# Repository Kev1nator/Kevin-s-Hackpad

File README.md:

# Kevin's-Hackpad

My hackpad includes 12 Keys, 1 Knob, a screen and a few LED's!

#3D Model

#PCB
Schematic:

PCB:

#Firmware
This hackpad uses [QMK](https://qmk.fm/) firmware for everything. 
-The rotary encoder cahnges volume. 
-The keys act as shortcuts for opening apps, exectuing commands, ...
-The OLED shows the time.

#BOM:
Here you can find all the parts you need for this hackpad

- 4x Cherry MX Switches
- 4x DSA Keycaps
- 8x WS2812B LEDs
- 1x 0.91" 128x32 OLED Display
- 1x EC11 Rotary Encoder
- 1x XIAO RP2040
- 1x Case (3 printed parts)

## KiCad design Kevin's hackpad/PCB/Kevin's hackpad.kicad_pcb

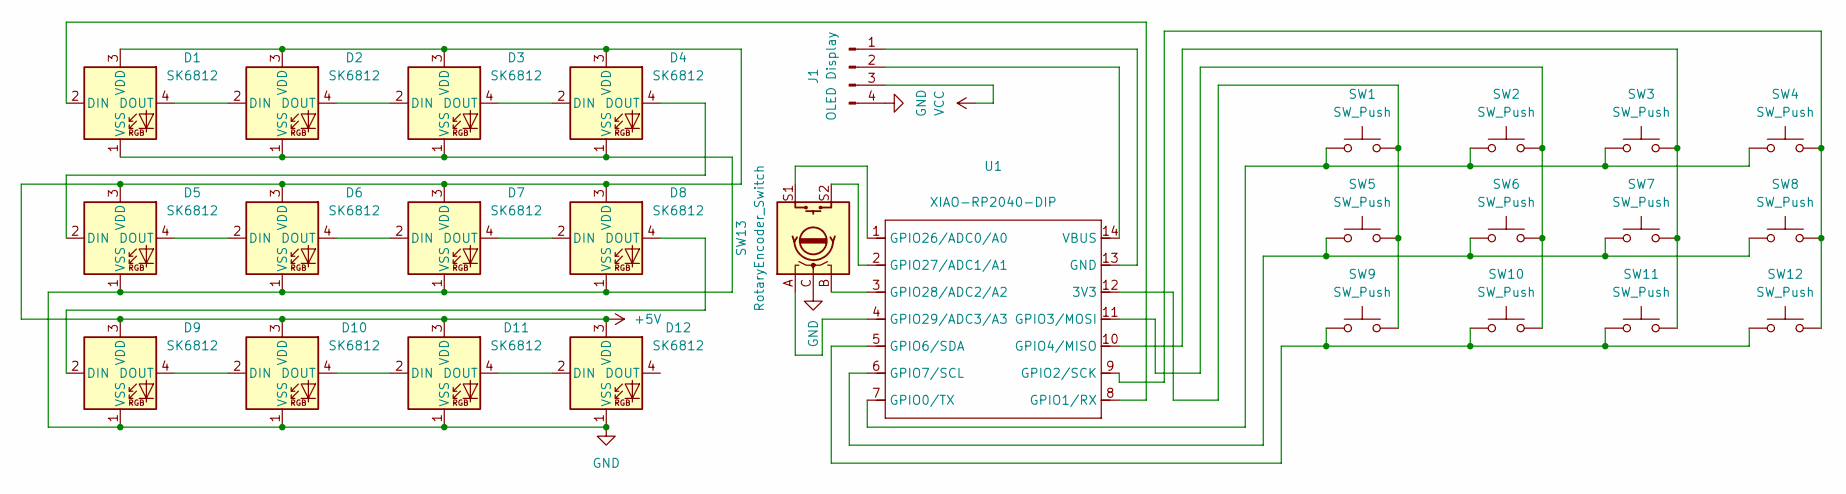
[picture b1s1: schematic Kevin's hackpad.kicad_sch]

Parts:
D1, D2, D3, D4, D5, D6, D7, D8, D9, D10, D11, D12: SK6812; LED_SK6812MINI_PLCC4_3.5x3.5mm_P1.75mm
J1: OLED Display; SSD1306-0.91-OLED-4pin-128x32
SW1, SW2, SW3, SW4, SW5, SW6, SW7, SW8, SW9, SW10, SW11, SW12: SW_Push; SW_Cherry_MX_1.00u_PCB
SW13: RotaryEncoder_Switch; RotaryEncoder_Alps_EC11E-Switch_Vertical_H20mm
U1: XIAO-RP2040-DIP

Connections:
+5V: D1.3 (VDD), D2.3 (VDD), D3.3 (VDD), D4.3 (VDD), D5.3 (VDD), D6.3 (VDD), D7.3 (VDD), D8.3 (VDD), D9.3 (VDD), D10.3 (VDD), D11.3 (VDD), D12.3 (VDD)
GND: D1.1 (VSS), D2.1 (VSS), D3.1 (VSS), D4.1 (VSS), D5.1 (VSS), D6.1 (VSS), D7.1 (VSS), D8.1 (VSS), D9.1 (VSS), D10.1 (VSS), D11.1 (VSS), D12.1 (VSS), J1.4, SW13.C
unnamed: D1.2 (DIN), U1.8 (GPIO1/RX)
unnamed: D1.4 (DOUT), D2.2 (DIN)
unnamed: D2.4 (DOUT), D3.2 (DIN)
unnamed: D3.4 (DOUT), D4.2 (DIN)
unnamed: D4.4 (DOUT), D5.2 (DIN)
unnamed: D5.4 (DOUT), D6.2 (DIN)
unnamed: D6.4 (DOUT), D7.2 (DIN)
unnamed: D7.4 (DOUT), D8.2 (DIN)
unnamed: D8.4 (DOUT), D9.2 (DIN)
unnamed: D9.4 (DOUT), D10.2 (DIN)
unnamed: D10.4 (DOUT), D11.2 (DIN)
unnamed: D11.4 (DOUT), D12.2 (DIN)
unnamed: J1.1, U1.13 (GND)
unnamed: J1.2, U1.14 (VBUS)
unnamed: SW1.2, SW5.2, SW9.2, U1.12 (3V3)
unnamed: SW1.1, SW2.1, SW3.1, SW4.1, U1.7 (GPIO0/TX)
unnamed: SW4.2, SW8.2, SW12.2, U1.9 (GPIO2/SCK)
unnamed: SW2.2, SW6.2, SW10.2, U1.11 (GPIO3/MOSI)
unnamed: SW3.2, SW7.2, SW11.2, U1.10 (GPIO4/MISO)
unnamed: SW9.1, SW10.1, SW11.1, SW12.1, U1.5 (GPIO6/SDA)
unnamed: SW5.1, SW6.1, SW7.1, SW8.1, U1.6 (GPIO7/SCL)
unnamed: SW13.S1, U1.1 (GPIO26/ADC0/A0)
unnamed: SW13.S2, U1.2 (GPIO27/ADC1/A1)
unnamed: SW13.B, U1.3 (GPIO28/ADC2/A2)
unnamed: SW13.A, U1.4 (GPIO29/ADC3/A3)
VCC: J1.3

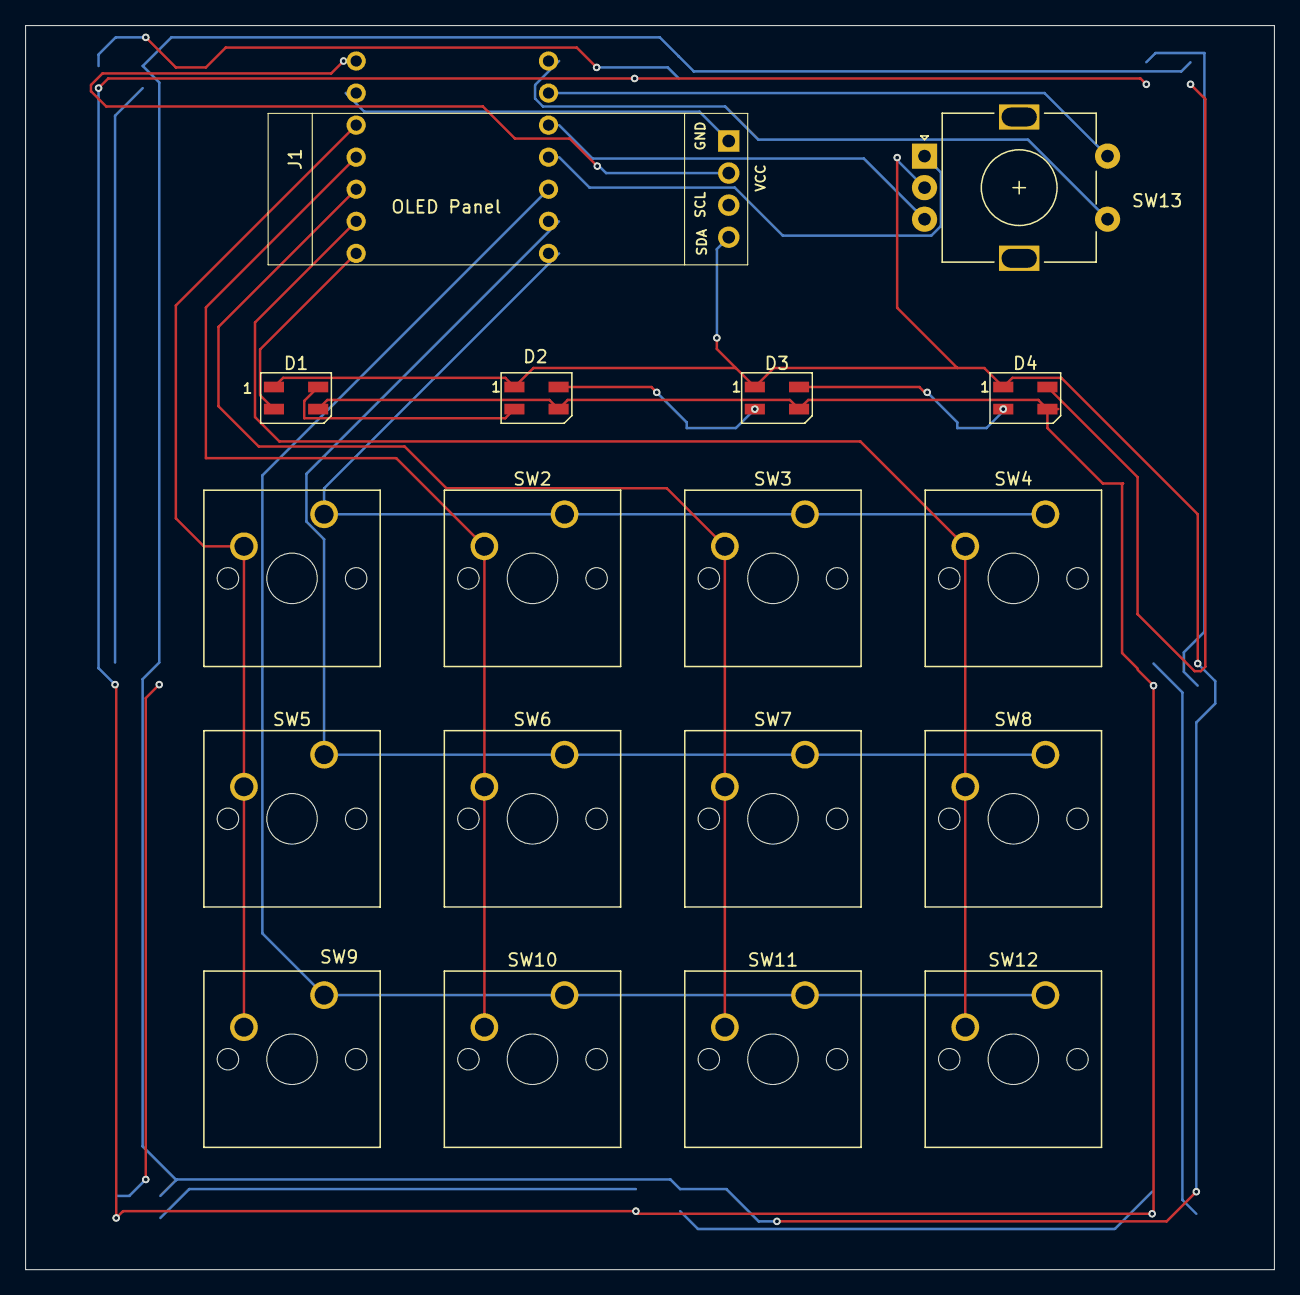
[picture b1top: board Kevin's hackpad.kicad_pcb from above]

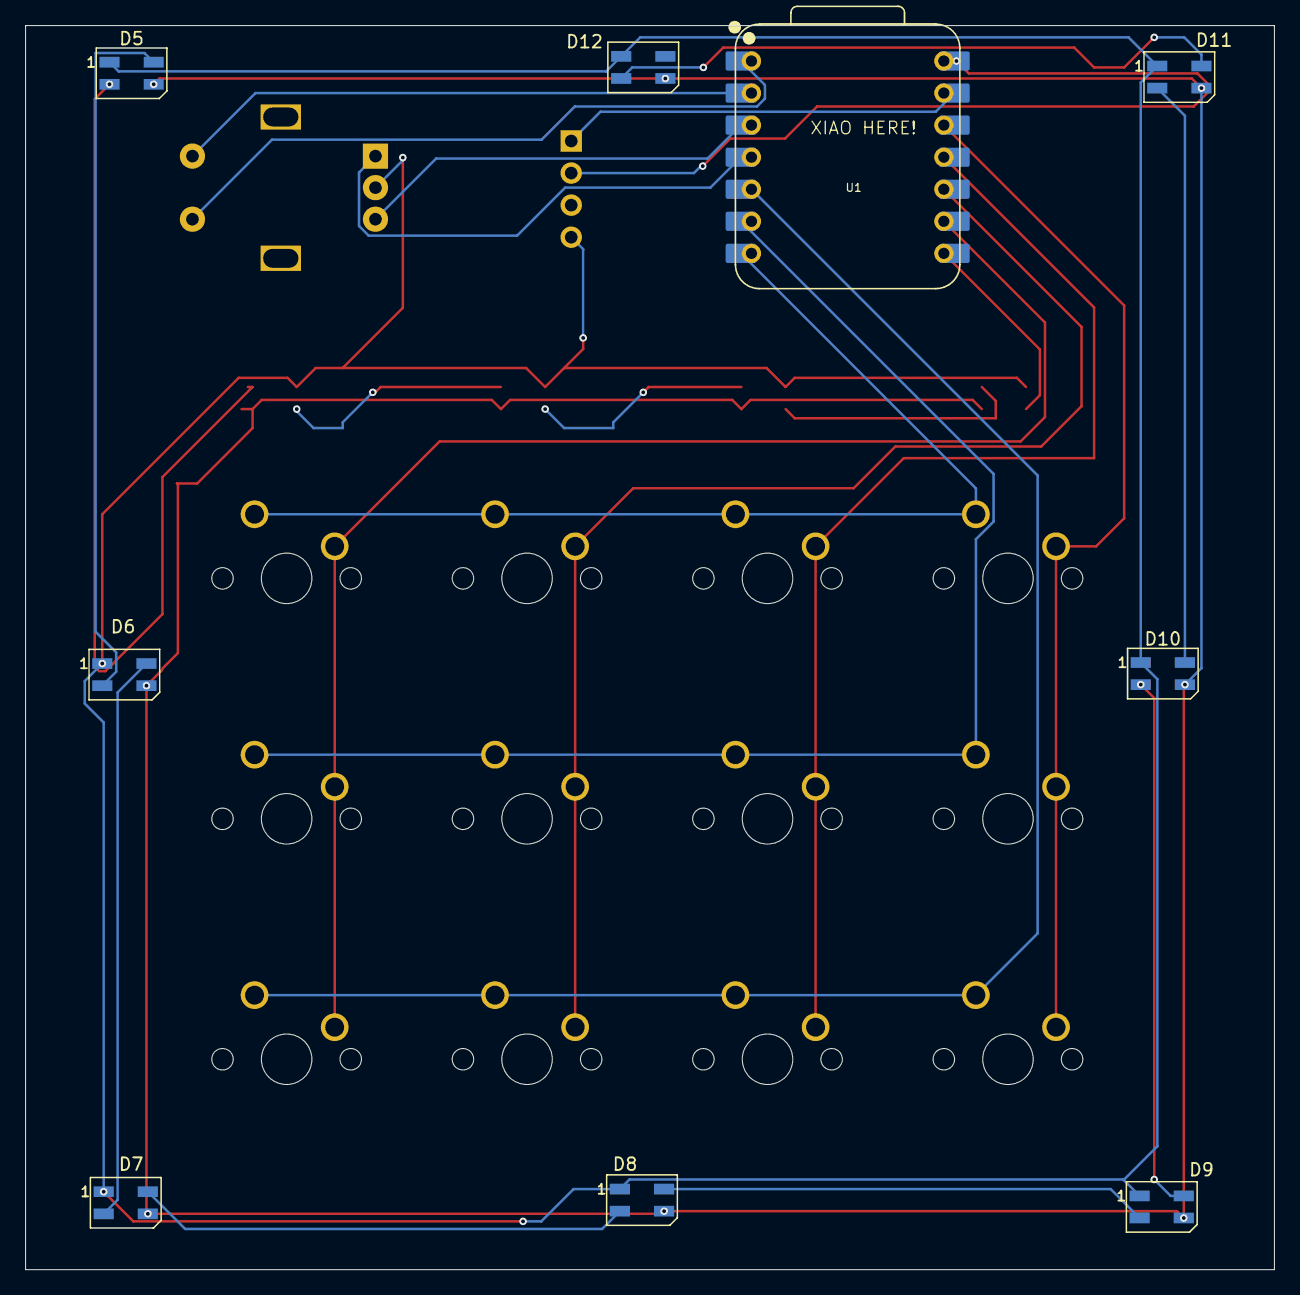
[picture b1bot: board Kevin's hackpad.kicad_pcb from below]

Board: 2 copper layers, 98.9 x 98.6 mm, 27 parts (9 on the bottom side), 27 nets.

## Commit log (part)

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2026-06-30 added Backcover v2
